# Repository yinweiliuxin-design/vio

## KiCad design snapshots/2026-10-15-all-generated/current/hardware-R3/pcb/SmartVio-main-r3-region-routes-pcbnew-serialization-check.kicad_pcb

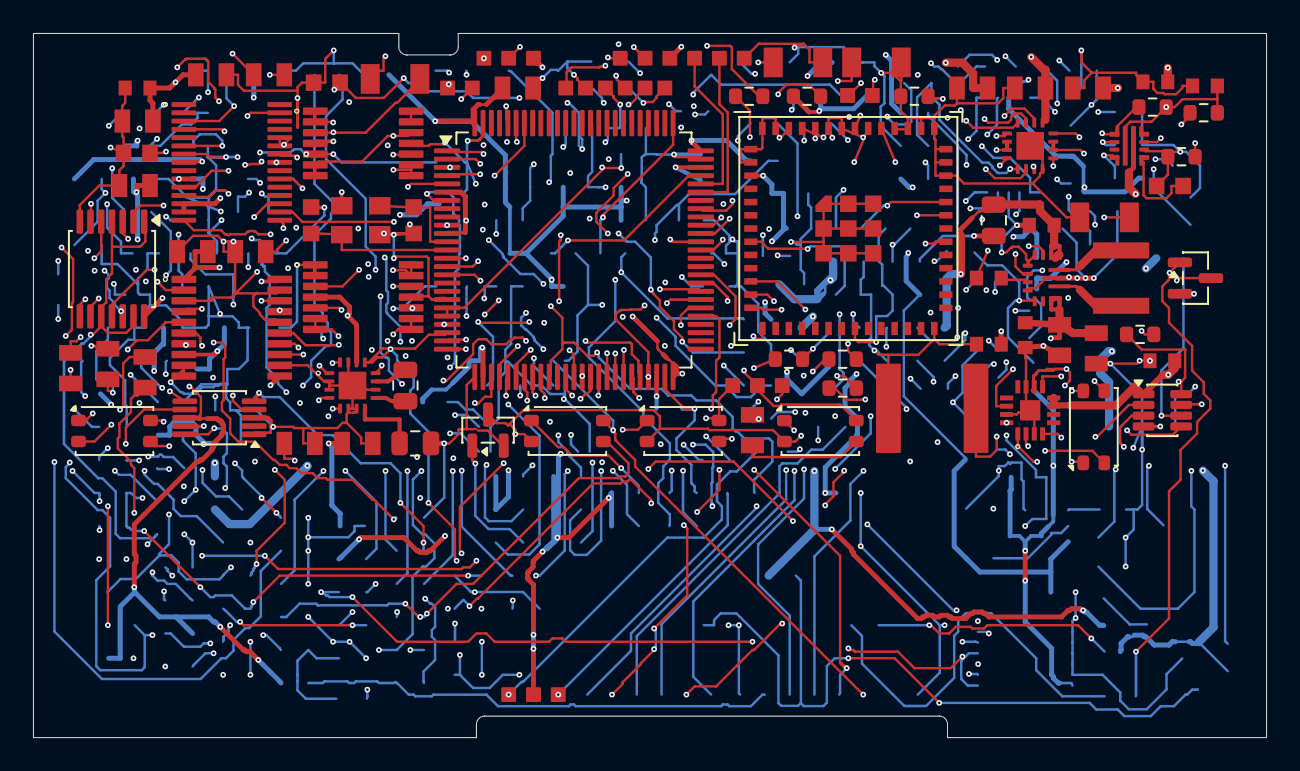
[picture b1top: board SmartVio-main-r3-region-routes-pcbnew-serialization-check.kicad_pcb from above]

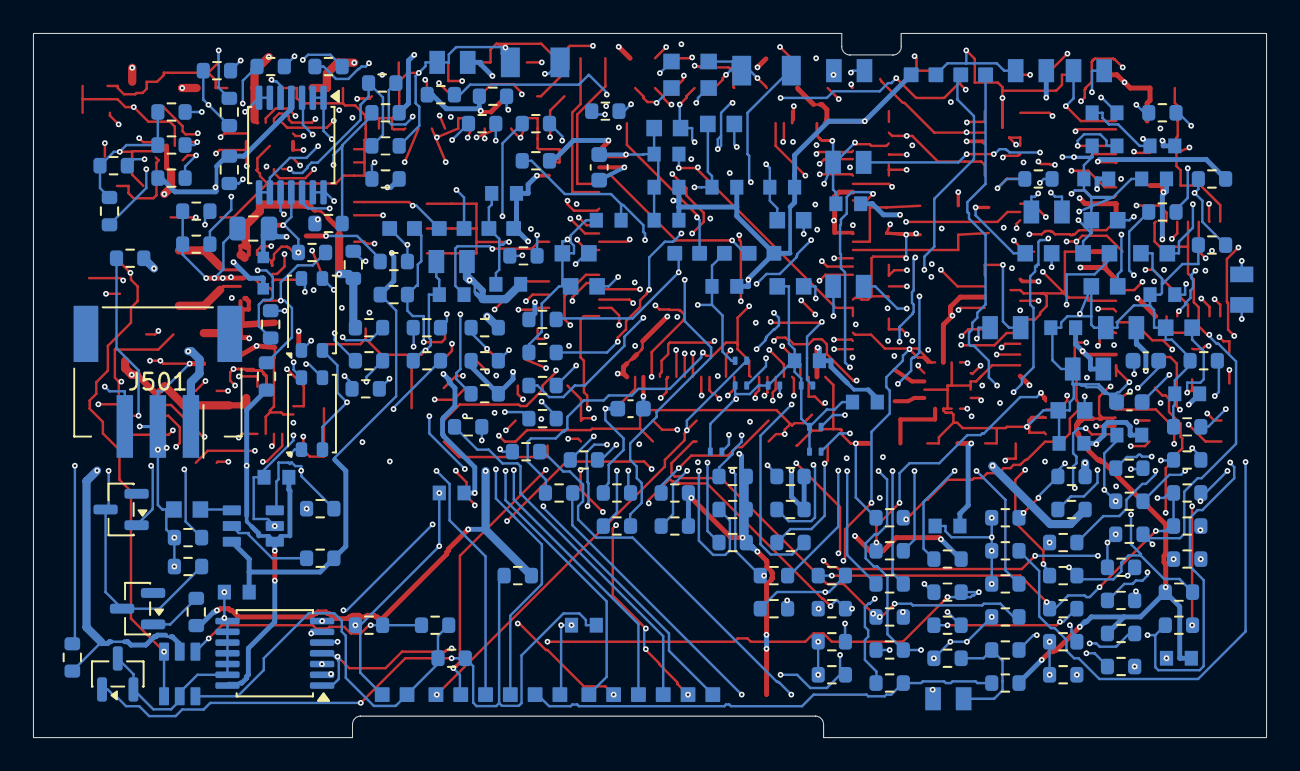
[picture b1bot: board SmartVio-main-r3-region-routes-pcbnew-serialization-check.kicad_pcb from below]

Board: 8 copper layers, 74.6 x 42.6 mm, 284 parts (205 on the bottom side), 206 nets.

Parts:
C101, C811, C830, C831, C832, C1302: 0.1uF C0G 25V 5%; C1206C104J3GACTU
C102: 10uF / 10V; CC0805KKX5R6BB106
C103, C240, C307, C1301: 100nF / 10V; CC0603KRX7R7BB104
C104, C111, C201, C202, C231, C232, C241, C301, C302: 1uF / 10V; CC0805KKX7R7BB105
C121, C211, C212, C502, C503: 10uF / 10V effective >=4.7uF; CC0805KKX5R6BB106
C221, C222: 4.7uF / 10V; CC0805KKX7R6BB475
C303: 1uF / 10V; C_0805_2012Metric
C304: 2.2uF / 10V X7R; Ceff_min >= C303_Ceff_max; C_0805_2012Metric
C305, C306: 2.2uF / 10V; CC0805KKX7R7BB225
C320, C821, C822, C823, C824, C825, C1701, C1702, C1703, C1704, C1705, C1706, C1707, C1708, C1901: 0.01uF C0G 25V 5%; C0603C103J3GACTU
C501: 4.7uF / 10V effective >=1uF; CC0805KKX7R6BB475
C601, C810, C901: 1uF; CC0603KRX7R7BB105
C602, C604, C606, C608, C703, C710, C712, C714, C801, C802, C803, C804, C805, C809, C902, C904, C1101, C1103, C1107, C1108: 100nF; CC0603KRX7R7BB104
C603, C605, C607, C711, C713, C715, C905: 10uF; CC0805KKX5R6BB106
C701, C702: 2.2uF; C_0603_1608Metric
C704, C705: 0.0022uF C0G 50V 5%; C0603C222J5GACTU
C806: 4.7uF; CC0805KKX7R6BB475
C807, C808: 2.2uF low ESR; C_0603_1608Metric
C812, C813: 3e-05uF C0G 50V 5%; C0603C300J5GACTU
C820: 0.001uF C0G 50V 5%; C0603C102J5GACTU
C903: 22uF; CC0805MKX5R6BB226
C1001: 0.0047uF C0G 50V 5%; C0603C472J5GACTU
C1002: 100nF 50V; CC0603KRX7R9BB104
C1003: 1uF 16V; CC0603KRX7R7BB105
C1102: 10uF 10V; C_0805_2012Metric
C1104, C1105: 22uF 10V; CC0805MKX5R6BB226
C1106: 22uF 10V; C_0805_2012Metric
C1303: 0.47uF C0G 50V 5%; C2220C474J5GACTU
C1709, C1710, C1711: 100nF 10V X7R; CC0603KRX7R7BB104
C1902: 2.2uF X7R 16V; effective>=1uF; CC0603KRX7R7BB225
C1903, C1904, C1921, C1922: 100nF X7R 16V; CC0603KRX7R7BB104
D1201, D1202, D1203, D1204, D1205, D1206, D1207: TPD1E10B06DPYR; TI_DPY0002A_1x0.6mm_P0.7mm_NSMD
D1301, D1302: low-leakage enable OR; SOT-23
FB1101: Ferrite 120R@100MHz / >=0.5A; 742792625
H_AUDIO_1_M: PROPOSED_HARNESS_ENDPOINT; WirePads_6_P1.5
H_AUDIO_2_M: PROPOSED_HARNESS_ENDPOINT; WirePads_3_P1.5
H_COVER_1_M: PROPOSED_HARNESS_ENDPOINT; WirePads_6_P1.2_R2
H_COVER_2_M: PROPOSED_HARNESS_ENDPOINT; WirePads_6_P1.5
H_COVER_3_M: PROPOSED_HARNESS_ENDPOINT; WirePads_3_P1.5
H_USB_1_M: PROPOSED_HARNESS_ENDPOINT; WirePads_6_P1.5
H_USB_2_M: PROPOSED_HARNESS_ENDPOINT; WirePads_3_P1.5
J101: Existing pickup / polarity TBD; WirePads_2_P1.5
J501: JST PH 3-way internal2A AWG24 pack header; JST_PH_S3B_PH_SM4_TB_OfficialLand_3P
J801: SWD test pads; WirePads_5_P1.5
J901: Speaker harness; WirePads_2_P1.5
J902: RF factory pads - not user connector; WirePads_6_P1.5
J1801: Internal thermal sensor harness endpoint; WirePads_4_P1.5
J1921: RT1921 harness solder endpoint; WirePads_2_P1.5
K1201, K1202: AQY221R6VY; Panasonic_APV-AQY_SSOP-4_4.45x2.65mm_P1.27mm
K1203, K1204, K1205, K1206, K1207: AQY221R2VY; Panasonic_APV-AQY_SSOP-4_4.45x2.65mm_P1.27mm
L1101: 1.5uH / Isat >=5A candidate; XGL4020-152MEC
Q1201: PMV30UN2R; SOT-23
Q1601: PMV30UN2; SOT-23
R101, R103, R104, R201, R202, R241, R242, R311, R312, R503, R504, R802, R803, R820, R821, R822, R823, R824, R826, R901, R902, R1002, R1004, R1301: 10k; R_0603_1608Metric
R102: 4.7M; R_0603_1608Metric
R111: 100; R_0603_1608Metric
R121, R211, R212: 220; R_0603_1608Metric
R122, R221, R222, R320, R321, R505, R506, R590, R703, R816, R817, R903, R904, R1006, R1104, R1211, R1302, R1602: 100k; R_0603_1608Metric
R231, R232, R301, R302: 22k; R_0603_1608Metric
R290, R291: 15k; R_0603_1608Metric
R322, R830, R831, R832, R850, R851, R852, R1210, R1603, R1604: 1k; R_0603_1608Metric
R501: 2000ohm 0.1% 25ppm/C; R_0603_1608Metric
R502: 1500ohm 0.1% 25ppm/C; R_0603_1608Metric
R601: 0R; R_0603_1608Metric
R602, R603: 4.7k; R_0603_1608Metric
R691, R810, R811, R812, R813, R814, R815, R906: 33R initial; R_0603_1608Metric
R701, R702, R907: 470R; R_0603_1608Metric
R801: 10R; R_0603_1608Metric
R905: 2k; R_0603_1608Metric
R1001: 26.1k; R_0603_1608Metric
R1003: 37.4k; R_0603_1608Metric
R1005: 6.65k; R_0603_1608Metric
R1101: 312k; 0.1%; <=25ppm/K; exact MPN pending; R_0603_1608Metric
R1102: 100k; 0.1%; <=25ppm/K; exact MPN pending; R_0603_1608Metric
R1103, R1303: 33k 1%; R_0603_1608Metric
R1201, R1202, R1203, R1204, R1205, R1206, R1207: 270R; R_0603_1608Metric
R1304, R1717, R1911, R1913, R1922: 100k 1%; R_0603_1608Metric
R1601: 4.7k 1%; R_0603_1608Metric
R1701, R1705, R1709: 15k 0.1% 25ppm/C; R_0603_1608Metric
R1702, R1706, R1710: 10k 0.1% 25ppm/C; R_0603_1608Metric
R1703, R1707, R1711: 100k 0.1% 25ppm/C; R_0603_1608Metric
R1704, R1708, R1712, R1716: 100R 1%; R_0603_1608Metric
R1715: 10M; 1%; ISET buffer bias, include in mirror cali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; R_0603_1608Metric
R1801, R1802: 33R 1%; R_0603_1608Metric
R1901, R1902, R1903, R1912: 1k 1%; R_0603_1608Metric
R1921: 158k 1%; R_0603_1608Metric
R1923: 8.2k 1%; R_0603_1608Metric
R1924: 30.1k 1%; R_0603_1608Metric
R2351: 499ohm 0.1% 25ppm/C; R_0603_1608Metric
R2352: 68100ohm 0.1% 25ppm/C; R_0603_1608Metric
U101, U201: TLV9064PWR; TI_PW0014A_Official
U301: TPA6132A2RTER; TI_RTE0016C_Official
U501: BQ24074RGTR; TI_RGT0016C_BQ24074_EP17
U601: PCM1864DBTR; TI_DBT0030A_Official
U701: PCM5102APWR; TI_PW0020A_Official
U801: STM32H743VIT6; LQFP-100_14x14mm_P0.5mm
U901: ESP32-MINI-1U
U902: MAX98357AETE+; ADI_T1633_4_Official
U1001: TPS259470LRPWR; TI_RPW0010A_TPS259470
U1101: TPS63070RNMR; TI_RNM0015A_TPS63070
U1301: LTC2954ITS8-1#TRPBF; TSOT-23-8
U1701: ADS1115IDGSR; MSOP-10_3x3mm_P0.5mm
U1702: TMUX1511PWR; TSSOP-14_4.4x5mm_P0.65mm
U1703: OPA4330AIPWR; TSSOP-14_4.4x5mm_P0.65mm
U1901: sequenced performance-domain supply; TI_DBV0006A_Official
U1902: audio I2C powered-domain isolation; TSSOP-14_4.4x5mm_P0.65mm
U1921: independent pack NTC window inhibits charge gate; TI_DDC0006A_Official
U1922: 2.5V independent NTC excitation reference; SOT-23
Y801: 24.576MHz CL18pF candidate; ABM8-24_576MHZ-B2-T

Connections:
ADC_1V8: C602.1, C603.1, U601.11 (LDO)
ADC_AUX_L_AC: C231.2, U601.4 (VINR1)
ADC_AUX_R_AC: C232.2, U601.29 (VINL3)
ADC_BCK: R811.2, U601.17 (BCK)
ADC_BCK_SRC: R811.1, U801.4 (PE5_SAI1SCK)
ADC_DATA: U601.18 (DOUT), U801.5 (PE6_SAI1SD)
ADC_DATA2: R691.2, U801.2 (PE3_SAI1_SD_B)
ADC_DATA2_SRC: R691.1, U601.21 (GPIO1)
ADC_FS: R810.2, U601.16 (LRCK)
ADC_FS_SRC: R810.1, U801.3 (PE4_SAI1FS)
ADC_PU_AC: C111.2, U601.3 (VINL1)
ADC_SCK: R812.2, U601.15 (SCKI)
ADC_SCK_SRC: R812.1, U801.66 (PC9_MCO2)
ADC_VREF: C601.1, U601.6 (VREF)
ADC_XI: R601.1, U601.10 (XI)
AUDIO_BUS_EN: R1913.1, U801.7 (PC13), U1902.1 (SEL1), U1902.4 (SEL2)
AUDIO_PWR_EN: R1911.1, U801.1 (PE2_AUDIO_PWR_EN), U1901.3 (ON)
BOOT0: R803.1, U801.94 (BOOT0)
BUCK_AUX: C1101.1, U1101.3 (VAUX)
BUCK_FB: R1101.2, R1102.1, U1101.5 (FB)
BUCK_L1: L1101.1, U1101.11 (L1)
BUCK_L2: L1101.2, U1101.9 (L2)
CC_FAULT_N: H_USB_1_M.5, U801.38 (PE8_CC_FAULT_N)
CELL_NTC_SENSE: J1921.1 (NTC_SENSE), R1921.1, R1924.2, U1921.3 (INA+)
CHARGE_ALLOW: R1601.1, U801.44 (PE14_CHARGE_ALLOW)
CHARGE_DISABLE: Q1601.3 (D), R503.2, U501.4 (CE)
CHARGE_GATE: Q1601.1 (G), R1601.2, R1602.1, U1921.1 (OUTA), U1921.6 (OUTB)
CHG_EN1: R590.1, R1603.2, U501.6 (EN1)
CHG_EN1_MCU: R1603.1, U801.42 (PE12_CHG_EN1)
CHG_EN2: R504.2, R1604.2, U501.5 (EN2)
CHG_EN2_MCU: R1604.1, U801.43 (PE13_CHG_EN2)
CHG_ITERM_ECO: R2351.1, U501.15 (ITERM)
CHG_PGOOD_N: R1902.2, U801.47 (PB11_CHG_PGOOD)
CHG_STATUS_N: R1903.2, U801.57 (PD10_CHG_STATUS)
CHG_TMR_ECO: R2352.1, U501.14 (TMR)
CHG_TP: R506.2, R1903.1, U501.9 (CHG)
DAC_1V8: C703.1, U701.18 (LDOO)
DAC_CPN: C701.2, U701.4 (CAPM)
DAC_CPP: C701.1, U701.2 (CAPP)
DAC_L: C201.1, C704.1, R301.1, R701.2
DAC_NEG: C702.1, U701.5 (VNEG)
DAC_R: C202.1, C705.1, R302.1, R702.2
DAC_RAW_L: R701.1, U701.6 (OUTL)
DAC_RAW_R: R702.1, U701.7 (OUTR)
DAC_UNMUTE: R703.1, U701.17 (XSMT), U801.22 (PA0)
EFUSE_DVDT: C1001.1, U1001.7 (DVDT)
EFUSE_ILM: R1005.1, U1001.9 (ILM)
FX_ADC: C832.1, R832.2, U801.16 (PC1_ADC123_INP11)
FX_RAW: H_COVER_1_M.1, R832.1
GND: C102.2, C103.2, C104.2, C240.2, C241.2, C304.2, C305.2, C306.2, C307.2, C320.2, C501.2, C502.2, C503.2, C601.2, C602.2, C603.2, C604.2, C605.2, C606.2, C607.2, C608.2, C702.2, C703.2, C704.2, C705.2, C710.2, C711.2, C712.2, C713.2, C714.2, C715.2, C801.2, C802.2, C803.2, C804.2, C805.2, C806.2, C807.2, C808.2, C809.2, C810.2, C811.2, C812.2, C813.2, C820.2, C821.2, C822.2, C823.2, C824.2, C825.2, C830.2, C831.2, C832.2, C901.2, C902.2, C903.2, C904.2, C905.2, C1001.2, C1002.2, C1003.2, C1101.2, C1102.2, C1103.2, C1104.2, C1105.2, C1106.2, C1107.2, C1108.2, C1301.2, C1302.2, C1303.2, C1701.2, C1702.2, C1703.2, C1704.2, C1705.2, C1706.2, C1707.2, C1708.2, C1709.2, C1710.2, C1711.2, C1901.2, C1902.2, C1903.2, C1904.2, C1921.2, C1922.2, D1201.2 (GND), D1202.2 (GND), D1203.2 (GND), D1204.2 (GND), D1205.2 (GND), D1206.2 (GND), D1207.2 (GND), H_AUDIO_1_M.1, H_COVER_1_M.2, H_USB_1_M.1, J101.2, J501.2 (PACK-), J801.3 (GND), J902.2 (GND), J1801.2 (GND), J1921.2 (RETURN), Q1201.2 (S), Q1601.2 (S), R104.2, R122.2, R221.2, R222.2, R311.2, R312.2, R320.2, R501.2, R502.2, R504.1, R590.2, R601.2, R703.2, R803.2, R817.2, R901.2, R904.2, R1002.2, R1004.2, R1005.2, R1102.2, R1211.2, R1302.2, R1304.2, R1602.2, R1702.2, R1703.2, R1706.2, R1707.2, R1710.2, R1711.2, R1715.2, R1717.2, R1911.2, R1913.2, R1922.2, R2351.2, R2352.2, U101.11 (V-), U201.11 (V-), U301.2 (INL+), U301.3 (INR+), U301.6 (G0), U301.7 (G1), U301.10 (PGND), U301.15 (SGND), U301.17 (PAD), U501.8 (VSS), U501.17 (PAD_GND), U601.7 (AGND), U601.12 (DGND), U601.25 (MS_AD), U601.26 (MD0), U701.3 (CPGND), U701.9 (AGND), U701.10 (DEMP), U701.12 (SCK), U701.16 (FMT), U701.19 (DGND), U801.10 (VSS), U801.19 (VSSA), U801.26 (VSS), U801.49 (VSS), U801.74 (VSS), U801.99 (VSS), U901.1 (GND), U901.2 (GND), U901.27 (GND), U901.38 (GND), U901.39 (GND), U901.40 (GND), U901.41 (GND), U901.42 (GND), U901.43 (GND), U901.44 (GND), U901.45 (GND), U901.46 (GND), U901.47 (GND), U901.48 (GND), U901.49 (GND), U901.50 (GND), U901.51 (GND), U901.52 (GND), U901.53 (GND), U901.54 (GND), U901.55 (GND), U902.3 (GND), U902.11 (GND), U902.15 (GND), U902.17 (PAD), U1001.8 (GND), U1101.1 (PS_SYNC), U1101.4 (GND), U1101.10 (PGND), U1101.15 (VSEL), U1301.4 (GND), U1701.1 (ADDR), U1701.3 (GND), U1702.7 (GND), U1703.11 (V_MINUS), U1901.2 (GND), U1902.7 (GND), U1902.8 (D3), U1902.9 (S3), U1902.10 (SEL3), U1902.11 (D4), U1902.12 (S4), U1902.13 (SEL4), U1921.2 (GND), U1922.2 (ANODE), U1922.3 (STAR_TIE_ANODE), Y801.2 (GND), Y801.4 (GND)
HP_ATT_L: C301.1, R301.2, R311.1
HP_ATT_R: C302.1, R302.2, R312.1
HP_CPN: C303.2, U301.9 (CPN)
HP_CPP: C303.1, U301.11 (CPP)
HP_DETECT_GPIO: C320.1, R322.2, U801.28 (PA4)
HP_DETECT_RAW: H_AUDIO_1_M.2, R321.2, R322.1
HP_EN_VALIDATED: R320.1, U301.13 (EN), U801.23 (PA1)
HP_IN_L: C301.2, U301.1 (INL-)
HP_IN_R: C302.2, U301.4 (INR-)
HP_L: K1201.3 (LOAD_A), U301.16 (OUTL)
HP_L_PORT: D1201.1 (IO), H_AUDIO_1_M.3, K1201.4 (LOAD_B)
HP_NEG: C304.1, U301.8 (HPVSS)
HP_POS: C305.1, U301.12 (HPVDD)
HP_R: K1202.3 (LOAD_A), U301.5 (OUTR)
HP_R_PORT: D1202.1 (IO), H_AUDIO_1_M.4, K1202.4 (LOAD_B)
HSE_IN: C812.1, U801.12 (PH0_OSC), Y801.1 (X1)
HSE_OUT: C813.1, U801.13 (PH1_OSC), Y801.3 (X2)
I2C_AUDIO_SCL: U601.24 (SCL), U1902.6 (D2)
I2C_AUDIO_SDA: U601.23 (SDA), U1902.3 (D1)
I2C_SCL: R603.1, R1801.1, U801.95 (PB8_I2C1SCL), U1701.10 (SCL), U1902.5 (S2)
I2C_SDA: R602.1, R1802.1, U801.96 (PB9_I2C1SDA), U1701.9 (SDA), U1902.2 (S1)
KEY_BT: C825.1, H_COVER_1_M.3, R824.2, U801.15 (PC0_KEY_BT)
KEY_FX: C821.1, H_COVER_1_M.4, R820.1, U801.29 (PA5)
KEY_MIX: C823.1, H_COVER_1_M.5, R822.1, U801.31 (PA7)
KEY_MODE: C822.1, H_COVER_1_M.6, R821.1, U801.30 (PA6)
KEY_PWR: C824.1, R823.1, U801.32 (PC4), U1301.5 (INT_N)
LED_ZONE_1: R850.1, U801.63 (PC6)
LED_ZONE_1_A: H_COVER_2_M.1, R850.2
LED_ZONE_2: R851.1, U801.64 (PC7)
LED_ZONE_2_A: H_COVER_2_M.2, R851.2
LED_ZONE_3: R852.1, U801.65 (PC8)
LED_ZONE_3_A: H_COVER_2_M.3, R852.2
LINE_AC_L: C201.2, R290.1
LINE_AC_R: C202.2, R291.1
LINE_BIAS_L: R201.1, R290.2, U201.3 (IN+_A)
LINE_BIAS_R: R202.1, R291.2, U201.5 (IN+_B)
LINE_BUF_L: C211.1, U201.1 (OUT_A), U201.2 (IN-_A)
LINE_BUF_R: C212.1, U201.6 (IN-_B), U201.7 (OUT_B)
LINE_L: K1203.3 (LOAD_A), R211.2, R221.1
LINE_L_PORT: D1203.1 (IO), H_AUDIO_1_M.5, K1203.4 (LOAD_B)
LINE_OUT_AC_L: C211.2, R211.1
LINE_OUT_AC_R: C212.2, R212.1
LINE_R: K1204.3 (LOAD_A), R212.2, R222.1
LINE_R_PORT: D1204.1 (IO), H_AUDIO_1_M.6, K1204.4 (LOAD_B)
LOAD_CT: C1901.1, U1901.4 (CT)
LOAD_QOD: R1912.2, U1901.5 (QOD)
MCU_VDDA: C809.1, C810.1, R801.2, U801.20 (VREF+), U801.21 (VDDA)
MON_BAT_ADC: C1704.1, R1708.2, U1701.5 (AIN1)
MON_BAT_BUF: R1708.1, U1703.6 (IN_B_MINUS), U1703.7 (OUT_B)
MON_BAT_BUF_IN: C1703.1, R1707.1, U1702.6 (D2), U1703.5 (IN_B_PLUS)
MON_BAT_DIV: R1705.2, R1706.1, U1702.5 (S2)
MON_ENABLE: R1717.1, U801.46 (PB10_MON_ENABLE), U1702.1 (SEL1), U1702.4 (SEL2), U1702.10 (SEL3), U1702.13 (SEL4)
MON_ICHG_ADC: C1708.1, R1716.2, U1701.7 (AIN3)
MON_ICHG_BUF: R1716.1, U1703.13 (IN_D_MINUS), U1703.14 (OUT_D)
MON_ICHG_BUF_IN: C1707.1, R1715.1, U1702.11 (D4), U1703.12 (IN_D_PLUS)
MON_SYS_ADC: C1706.1, R1712.2, U1701.6 (AIN2)
MON_SYS_BUF: R1712.1, U1703.8 (OUT_C), U1703.9 (IN_C_MINUS)
MON_SYS_BUF_IN: C1705.1, R1711.1, U1702.8 (D3), U1703.10 (IN_C_PLUS)
MON_SYS_DIV: R1709.2, R1710.1, U1702.9 (S3)
MON_USB_ADC: C1702.1, R1704.2, U1701.4 (AIN0)
MON_USB_BUF: R1704.1, U1703.1 (OUT_A), U1703.2 (IN_A_MINUS)
MON_USB_BUF_IN: C1701.1, R1703.1, U1702.3 (D1), U1703.3 (IN_A_PLUS)
MON_USB_DIV: R1701.2, R1702.1, U1702.2 (S1)
NRST: C811.1, J801.5 (NRST), R802.1, U801.14 (NRST)
NTC_COLD_DIV: R1921.2, R1922.1, U1921.4 (INB-)
PACK_NTC: J501.3 (NTC), U501.1 (TS)
PACK_PLUS: C503.1, J501.1 (PACK+), R1705.1, U501.2 (BAT), U501.3 (BAT)
PGOOD_TP: R505.2, R1902.1, U501.7 (PGOOD)
PLAY_BCK: R815.2, U701.13 (BCK), U901.14 (IO26), U902.16 (BCLK)
PLAY_BCK_SRC: R815.1, U801.60 (PD13_SAI2SCK)
PLAY_DATA: R813.2, U701.14 (DIN), U901.33 (IO22)
PLAY_DATA_SRC: R813.1, U801.58 (PD11_SAI2SD)
PLAY_FS: R814.2, U701.15 (LRCK), U901.13 (IO25), U902.14 (LRCLK)
PLAY_FS_SRC: R814.1, U801.59 (PD12_SAI2FS)
PORT_ENABLE: R1210.1, U801.25 (PA3)
PU_ADC_COUPLE: C111.1, R111.2
PU_BIAS: C101.2, R102.1, U101.3 (IN+_A)
PU_BUF: R111.1, U101.1 (OUT_A), U101.2 (IN-_A), U101.10 (IN+_C)
PWR_BOOT_OK: R1301.1, U801.37 (PE7_BOOT_OK)
PWR_KILL: R1301.2, R1302.1, U1301.8 (KILL)
PWR_LTC_EN: D1301.1 (A), R1103.2, U1301.6 (EN)
PWR_ONT: C1302.1, U1301.3 (ONT)
PWR_PB: H_COVER_2_M.4, R826.2, U1301.2 (PB)
PWR_PDT: C1303.1, U1301.7 (PDT)
PZ_LIMIT: C101.1, R101.2
PZ_RAW: J101.1, R101.1
RETURN_L: C221.1, K1206.3 (LOAD_A)
RETURN_L_PORT: D1206.1 (IO), H_AUDIO_2_M.1, K1206.4 (LOAD_B)
RETURN_R: C222.1, K1207.3 (LOAD_A)
RETURN_R_PORT: D1207.1 (IO), H_AUDIO_2_M.2, K1207.4 (LOAD_B)
RET_AC_L: C221.2, R231.1
RET_AC_R: C222.2, R232.1
RET_BIAS_L: R231.2, R241.1, U201.10 (IN+_C)
RET_BIAS_R: R232.2, R242.1, U201.12 (IN+_D)
RET_BUF_L: C231.1, U201.8 (OUT_C), U201.9 (IN-_C)
RET_BUF_R: C232.1, U201.13 (IN-_D), U201.14 (OUT_D)
RF_BOOT: J902.5 (BOOT), R902.1, U901.21 (IO0)
RF_CHIP_EN: C901.1, J902.6 (EN), R901.1, R907.2, U901.8 (EN)
RF_ENABLE: R907.1, U801.33 (PC5)
RF_PROG_RX: J902.3 (RX_IN), U901.35 (RXD0)
RF_PROG_TX: J902.4 (TX_OUT), U901.36 (TXD0)
RF_RX: U801.55 (PD8_USART3TX), U901.11 (IO32_UART_RX)
RF_TX: U801.56 (PD9_USART3RX), U901.12 (IO33_UART_TX)
RILIM: R502.1, U501.12 (ILIM)
RISET: R501.1, U501.16 (ISET), U1702.12 (S4)
SEND_AC: C121.2, R121.1
SEND_BUF: C121.1, U101.8 (OUT_C), U101.9 (IN-_C)
SEND_T: K1205.3 (LOAD_A), R121.2, R122.1
SEND_T_PORT: D1205.1 (IO), H_AUDIO_2_M.3, K1205.4 (LOAD_B)
SPK_DATA: R906.2, U902.1 (DIN)
SPK_DATA_SRC: R906.1, U801.41 (PE11_SAI2_SD_B)
SPK_ENABLE: R905.1, U801.24 (PA2)
SPK_GAIN: R903.1, U902.2 (GAIN_SLOT)
SPK_N: H_COVER_2_M.5, J901.2 (SPK-), U902.10 (OUTN)
SPK_P: H_COVER_2_M.6, J901.1 (SPK+), U902.9 (OUTP)
SPK_SD_PIN: R904.1, R905.2, U902.4 (SD_MODE)
SSR_GATE: Q1201.1 (G), R1210.2, R1211.1
SSR_LED_0: K1201.1 (LED_A), R1201.2
SSR_LED_1: K1202.1 (LED_A), R1202.2
SSR_LED_2: K1203.1 (LED_A), R1203.2
SSR_LED_3: K1204.1 (LED_A), R1204.2
SSR_LED_4: K1205.1 (LED_A), R1205.2
SSR_LED_5: K1206.1 (LED_A), R1206.2
SSR_LED_6: K1207.1 (LED_A), R1207.2
SSR_SINK: K1201.2 (LED_K), K1202.2 (LED_K), K1203.2 (LED_K), K1204.2 (LED_K), K1205.2 (LED_K), K1206.2 (LED_K), K1207.2 (LED_K), Q1201.3 (D)
SWCLK: J801.4 (SWCLK), U801.76 (PA14_SWCLK)
SWDIO: J801.2 (SWDIO), U801.72 (PA13_SWDIO)
SYS: C502.1, C904.1, C905.1, C1102.1, C1103.1, C1301.1, C1921.1, R503.1, R826.1, R903.2, R1103.1, R1709.1, U501.10 (OUT), U501.11 (OUT), U902.7 (VDD), U902.8 (VDD), U1101.12 (VIN), U1101.13 (VIN), U1301.1 (VIN), U1921.5 (VDD)
SYS_ENABLE: D1301.3 (K), D1302.3 (K), R1304.1, U1101.14 (EN)
TEMP_REF2V5: C1922.1, R1923.2, R1924.1, U1922.1 (CATHODE)
TEMP_SCL: J1801.3 (SCL), R1801.2
TEMP_SDA: J1801.4 (SDA), R1802.2
TONE_ADC: C831.1, R831.2, U801.35 (PB1)
TONE_RAW: H_COVER_3_M.1, R831.1
UNUSED_BUF: U101.13 (IN-_D), U101.14 (OUT_D)
USB_5V_SAFE: C501.1, C1003.1, H_USB_2_M.2, R816.1, R1303.1, R1701.1, R1923.1, U501.13 (IN), U1001.6 (OUT)
USB_DATA_DISABLE: H_USB_1_M.6, U801.40 (PE10_USB_DATA_DISABLE)
USB_DATA_FAULT_N: H_USB_2_M.1, U801.39 (PE9_USB_DATA_FAULT_N)
USB_DM_MCU: H_USB_1_M.2, U801.70 (PA11_USBDM)
USB_DP_MCU: H_USB_1_M.3, U801.71 (PA12_USBDP)
USB_FLT: R1006.1, R1901.1, U1001.4 (FLT)
USB_FLT_MCU: R1901.2, U801.45 (PE15_USB_FLT)
USB_OV: R1003.2, R1004.1, U1001.2 (OVLO)
USB_UV: R1001.2, R1002.1, U1001.1 (EN_UVLO)
USB_WAKE_A: D1302.1 (A), R1303.2
V3A: C103.1, C104.1, C240.1, C241.1, C306.1, C307.1, C604.1, C605.1, C710.1, C711.1, C712.1, C713.1, C1106.1, C1107.1, FB1101.2, R103.1, U101.4 (V+), U201.4 (V+), U301.14 (VDD), U601.8 (AVDD), U701.1 (CPVDD), U701.8 (AVDD)
V3D: C801.1, C802.1, C803.1, C804.1, C805.1, C806.1, C1104.1, C1105.1, C1108.1, C1709.1, C1710.1, C1711.1, C1902.1, C1904.1, H_COVER_3_M.2, H_USB_1_M.4, J801.1 (VTREF), J1801.1 (3V3), R321.1, R505.1, R506.1, R602.2, R603.2, R801.1, R802.2, R820.2, R821.2, R822.2, R823.2, R824.1, R1006.2, R1101.1, R1104.2, R1201.1, R1202.1, R1203.1, R1204.1, R1205.1, R1206.1, R1207.1, U801.6 (VBAT), U801.11 (VDD), U801.27 (VDD), U801.50 (VDD), U801.75 (VDD), U801.100 (VDD), U1101.7 (VOUT), U1101.8 (VOUT), U1701.8 (VDD), U1702.14 (VDD), U1703.4 (V_PLUS), U1901.1 (VIN), U1902.14 (VDD)
V3LOAD: C606.1, C607.1, C608.1, C714.1, C715.1, C902.1, C903.1, C1903.1, FB1101.1, J902.1 (3V3), R902.2, R1912.1, U601.13 (DVDD), U601.14 (IOVDD), U701.11 (FLT), U701.20 (DVDD), U901.3 (3V3), U1901.6 (VOUT)
V3_PG: R1104.1, U1101.2 (PG)
VBUS_RAW: C1002.1, H_USB_2_M.3, R1001.1, R1003.1, U1001.5 (IN)
VBUS_SENSE: C820.1, R816.2, R817.1, U801.68 (PA9_VBUS)
VCAP1: C807.1, C808.1, U801.48 (VCAP1), U801.73 (VCAP2)
VMID: R102.2, R201.2, R202.2, R241.2, R242.2, U101.6 (IN-_B), U101.7 (OUT_B), U101.12 (IN+_D)
VMID_DIV: C102.1, R103.2, R104.1, U101.5 (IN+_B)
VOL_ADC: C830.1, R830.2, U801.34 (PB0)
VOL_RAW: H_COVER_3_M.3, R830.1

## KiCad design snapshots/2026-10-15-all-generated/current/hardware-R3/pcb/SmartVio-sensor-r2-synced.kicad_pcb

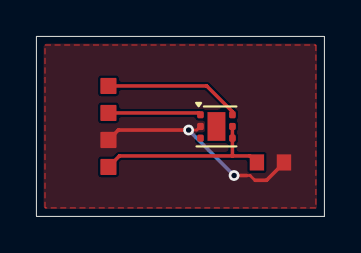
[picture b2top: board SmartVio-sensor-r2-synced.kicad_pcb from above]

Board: 2 copper layers, 16.0 x 10.0 mm, 3 parts (0 on the bottom side), 4 nets.

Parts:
C1801: 100nF 10V X7R; CC0603KRX7R7BB104
J1802: Internal thermal sensor harness endpoint; WirePads_4_P1.5
U1801: TMP117AIDRVR; WSON-6-1EP_2x2mm_P0.65mm_EP1x1.6mm

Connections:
GND: C1801.2, J1802.2 (GND), U1801.2 (GND)
TEMP_SCL: J1802.3 (SCL), U1801.1 (SCL)
TEMP_SDA: J1802.4 (SDA), U1801.6 (SDA)
V3D: C1801.1, J1802.1 (3V3), U1801.4 (ADD0), U1801.5 (V_PLUS)

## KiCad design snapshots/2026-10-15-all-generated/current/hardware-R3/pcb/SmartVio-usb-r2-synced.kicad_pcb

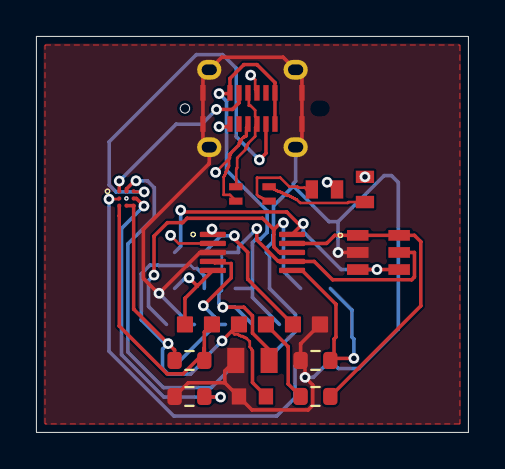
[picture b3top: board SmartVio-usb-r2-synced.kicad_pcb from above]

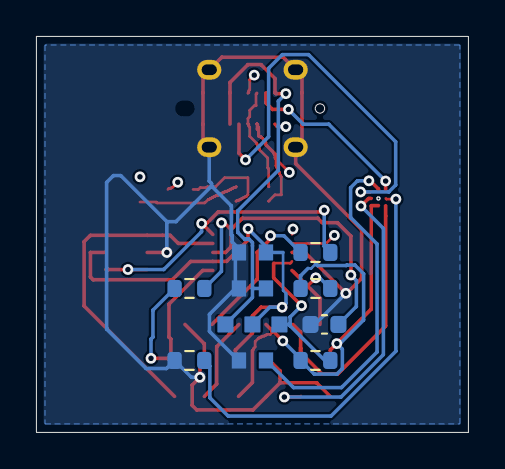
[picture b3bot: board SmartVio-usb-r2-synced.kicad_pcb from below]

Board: 4 copper layers, 24.0 x 22.0 mm, 24 parts (10 on the bottom side), 24 nets.

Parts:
C401, C1401: 100nF / 50V X7R; CC0603KRX7R9BB104
C403: 100nF / 10V X7R; local U401.5 bypass; CC0603KRX7R7BB104
C1402: 1uF / 10V; CC0603KRX7R7BB105
C1501: 2.2uF 16V X7R; effective 1..10uF; CC0805KKX7R7BB225
C1502: 1uF 10V X7R; effective 0.3..3uF; C_0603_1608Metric
FL1501: 90 ohm at 100MHz candidate; ACM2012H-900-2P-T06
H_USB_1_R: PROPOSED_HARNESS_ENDPOINT; WirePads_6_P1.5
H_USB_2_R: PROPOSED_HARNESS_ENDPOINT; WirePads_3_P1.5
J401: USB4120-03-C; GCT_USB4120_Official_A6
L1501, L1502: 10nH matched candidate; 0603HP-10NXGRW
R401, R402: 5.1k; R_0603_1608Metric
R403, R404: 0R / tune at PHY; R_0603_1608Metric
R1401, R1502, R1503: 100k; R_0603_1608Metric
R1501: 24.9k 1%; R_0603_1608Metric
R1504: 140k 1%; R_0603_1608Metric
U401: USBLC6-2SC6; ST_USBLC6_2SC6_SOT23_6L_Official
U1401: TPD2S300YFFR; TI_YFF0009_Official
U1501: TPD2S703QDGSRQ1; TI_DGS0010A_Official

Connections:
CC1_PORT: J401.A5 (CC1), U1401.A1 (C_CC1)
CC1_SAFE: R401.1, U1401.B1 (CC1)
CC2_PORT: J401.B5 (CC2), U1401.A3 (C_CC2)
CC2_SAFE: R402.1, U1401.B3 (CC2)
CC_FAULT_N: H_USB_1_R.5, R1401.1, U1401.C1 (FLT_N)
CC_VBIAS: C1401.1, U1401.A2 (VBIAS)
GND: C401.2, C403.2, C1401.2, C1402.2, C1501.2, C1502.2, H_USB_1_R.1, J401.A1 (GND), J401.A12 (GND), J401.B1 (GND), J401.B12 (GND), J401.SH (SHELL), R401.2, R402.2, R1501.2, U401.2 (GND), U1401.B2 (GND), U1501.3 (GND)
USB_5V_SAFE: C403.1, C1501.1, H_USB_2_R.2, U401.5 (VBUS), U1501.7 (VPWR)
USB_DATA_DISABLE: H_USB_1_R.6, R1502.1, U1501.5 (EN_N)
USB_DATA_FAULT_N: H_USB_2_R.1, R1503.1, U1501.4 (FLT_N)
USB_DM_CMC: FL1501.3 (DM_OUT), L1502.1
USB_DM_CONN: FL1501.2 (DM_IN), J401.A7 (D-), J401.B7 (D-)
USB_DM_MCU: H_USB_1_R.2, R404.2
USB_DM_OVP_IN: L1502.2, U1501.1 (VD_MINUS)
USB_DM_SYS: R404.1, U401.3 (IO2), U401.4 (IO2), U1501.10 (D_MINUS)
USB_DP_CMC: FL1501.4 (DP_OUT), L1501.1
USB_DP_CONN: FL1501.1 (DP_IN), J401.A6 (D+), J401.B6 (D+)
USB_DP_MCU: H_USB_1_R.3, R403.2
USB_DP_OVP_IN: L1501.2, U1501.2 (VD_PLUS)
USB_DP_SYS: R403.1, U401.1 (IO1), U401.6 (IO1), U1501.9 (D_PLUS)
USB_OVP_MODE: R1501.1, R1504.2, U1501.6 (MODE)
USB_VREF: C1502.1, R1504.1, U1501.8 (VREF)
V3D: C1402.1, H_USB_1_R.4, R1401.2, R1502.2, R1503.2, U1401.C2 (VPWR), U1401.C3 (VM)
VBUS_RAW: C401.1, H_USB_2_R.3, J401.A4 (VBUS), J401.A9 (VBUS), J401.B4 (VBUS), J401.B9 (VBUS)
